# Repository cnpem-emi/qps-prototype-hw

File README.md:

This board was used for initial tests and conceptual validation of a quench extraction circuit for the SWLS.

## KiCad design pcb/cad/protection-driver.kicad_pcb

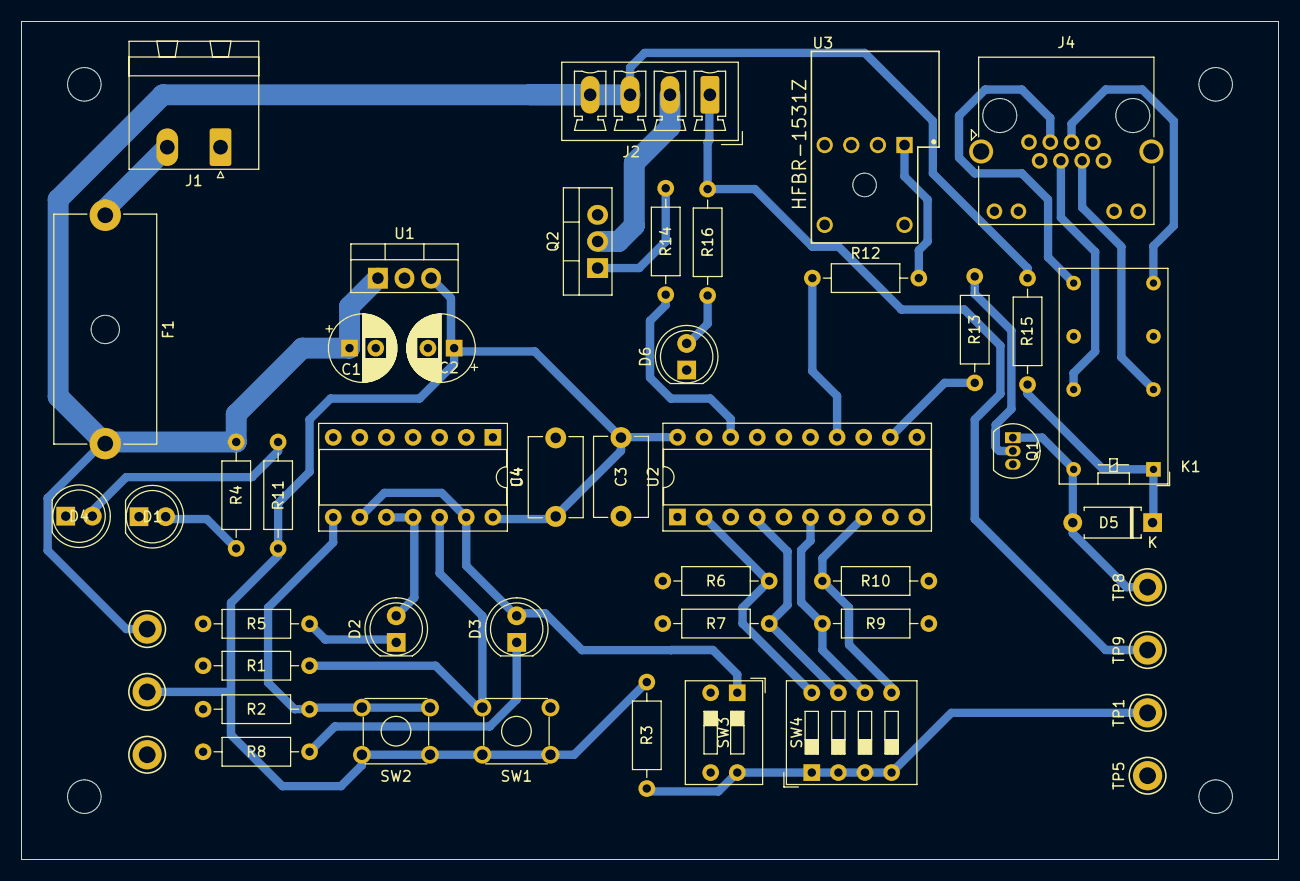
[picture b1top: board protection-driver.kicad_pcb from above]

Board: 2 copper layers, 120.0 x 80.0 mm, 48 parts (0 on the bottom side), 32 nets.

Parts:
C1, C2: 10u; CP_Radial_D6.3mm_P2.50mm
C3, C4: 100n; C_Disc_D7.5mm_W5.0mm_P7.50mm
D1, D2, D3, D4, D6: LED; LED_D5.0mm
D5: 1N4007; D_A-405_P7.62mm_Horizontal
F1: Fuse; Fuseholder_Cylinder-5x20mm_Schurter_0031_8201_Horizontal_Op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
J1: Vdc; PhoenixContact_MSTBA_2,5_2-G-5,08_1x02_P5.08mm_Horizontal
J2: contactor_1; PhoenixContact_MCV_1,5_4-G-3.81_1x04_P3.81mm_Vertical
J4: PS1; RJ45_Amphenol_RJHSE538X
K1: ML2RC2; Relay_DPDT_Omron_G5V-2
Q1: BC337; TO-92_Inline
Q2: TIP122; TO-220-3_Vertical
R1, R2, R6, R7, R9, R10: 2k; R_Axial_DIN0207_L6.3mm_D2.5mm_P10.16mm_Horizontal
R3: 100; R_Axial_DIN0207_L6.3mm_D2.5mm_P10.16mm_Horizontal
R4, R16: 1k5; R_Axial_DIN0207_L6.3mm_D2.5mm_P10.16mm_Horizontal
R5, R8, R11: 330; R_Axial_DIN0207_L6.3mm_D2.5mm_P10.16mm_Horizontal
R12: 180; R_Axial_DIN0207_L6.3mm_D2.5mm_P10.16mm_Horizontal
R13: 18k; R_Axial_DIN0207_L6.3mm_D2.5mm_P10.16mm_Horizontal
R14: 150; R_Axial_DIN0207_L6.3mm_D2.5mm_P10.16mm_Horizontal
R15: 70; R_Axial_DIN0207_L6.3mm_D2.5mm_P10.16mm_Horizontal
SW1, SW2: SW_Push_Dual_x2; SW_TH_Tactile_Omron_B3F-10xx
SW3: SW_SPST; SW_DIP_SPSTx02_Slide_9.78x7.26mm_W7.62mm_P2.54mm
SW4: Protect_sel; SW_DIP_SPSTx04_Slide_9.78x12.34mm_W7.62mm_P2.54mm
TP1, TP2, TP3, TP4, TP5, TP8, TP9: TestPoint; TestPoint_Keystone_5010-5014_Multipurpose
U1: LM7805; TO-220-3_Vertical
U2: 74HC240; DIP-20_W7.62mm_Socket
U3: HFBR-1531Z; Broadcom-HFBR-1531Z-MFG
U4: 7402; DIP-14_W7.62mm_Socket

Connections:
+5V: C2.1, C3.1, C4.1, R3.1, R11.1, SW1.1 (C), SW2.1 (C), TP2.1, U1.3 (VO), U2.20 (VCC), U4.14 (VCC)
+15V: C1.1, F1.2, J2.3, J2.4, R4.1, R15.1, TP3.1, U1.1 (VI)
/IGBT: R12.1, U2.14 (1Y2)
/K11: J4.5, K1.8
/K12: J4.6, K1.4
/K21: J4.3, K1.9
/K22: J4.4, K1.13
/PS_interlock: R13.1, U2.12 (1Y3)
/Q: D3.2 (A), SW3.1 (A), U4.9, U4.13
/R: R2.1, SW2.2 (D), U4.8
/S: R1.1, SW1.2 (D), U4.12
/contactor_1: R14.1, U2.18 (1Y0)
/~Q: D2.2 (A), U4.10, U4.11
GND: C1.2, C2.2, C3.2, C4.2, D1.1 (K), D4.1 (K), D6.1 (K), J1.1, Q1.3 (E), Q2.3 (E), R1.2, R2.2, R5.2, R6.2, R7.2, R8.2, R9.2, R10.2, TP4.1, TP5.1, U1.2 (GND), U2.1 (1OE), U2.10 (GND), U2.15 (2A1), U2.17 (2A0), U2.19 (2OE), U3.2 (Cathode), U3.3 (Open), U3.4 (Open), U4.2, U4.3, U4.5, U4.6, U4.7 (GND)
unnamed: D1.2 (A), R4.2
unnamed: D2.1 (K), R5.1
unnamed: D3.1 (K), R8.1
unnamed: D4.2 (A), R11.2
unnamed: D5.1 (K), K1.1, R15.2
unnamed: D5.2 (A), K1.16, Q1.1 (C), TP8.1
unnamed: D6.2 (A), R16.2
unnamed: F1.1, J1.2
unnamed: J2.1, R16.1, TP9.1
unnamed: J2.2, Q2.2 (C)
unnamed: Q1.2 (B), R13.2
unnamed: Q2.1 (B), R14.2
unnamed: R3.2, SW3.2 (B), SW4.1, SW4.2, SW4.3, SW4.4, TP1.1
unnamed: R6.1, SW4.8, U2.2 (1A0)
unnamed: R7.1, SW4.7, U2.4 (1A1)
unnamed: R9.1, SW4.6, U2.6 (1A2)
unnamed: R10.1, SW4.5, U2.8 (1A3)
unnamed: R12.2, U3.1 (Anode)

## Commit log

2022-08-29 Adds gitignore file
2023-01-20 schematic formatting
2024-06-11 Include driver for second contactor with delayed activation
